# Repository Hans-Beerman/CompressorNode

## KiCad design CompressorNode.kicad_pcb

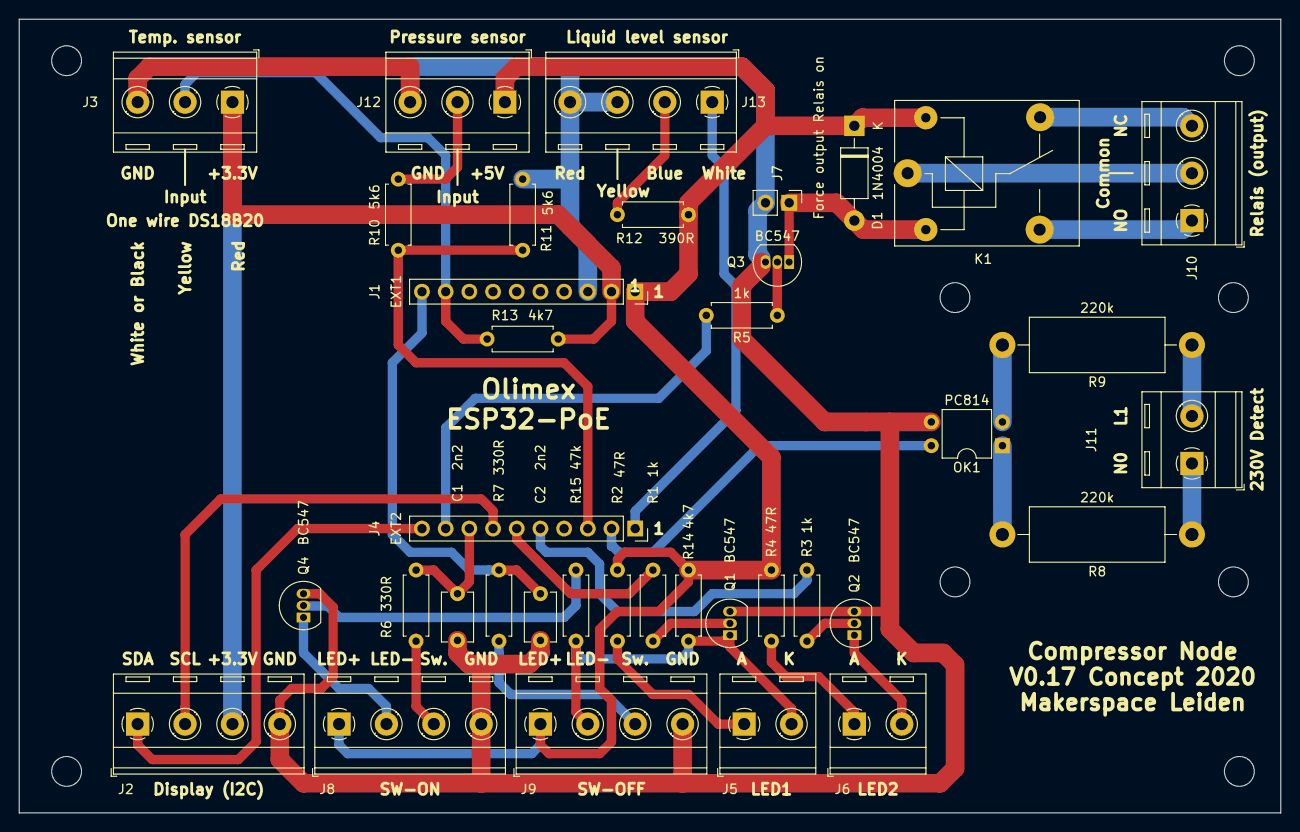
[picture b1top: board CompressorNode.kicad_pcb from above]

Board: 2 copper layers, 135.3 x 85.1 mm, 37 parts (0 on the bottom side), 35 nets.

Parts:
C1, C2: 2n2; C_Disc_D5.1mm_W3.2mm_P5.00mm
D1: 1N4004; D_DO-41_SOD81_P10.16mm_Horizontal
J1: EXT1; PinSocket_1x10_P2.54mm_Vertical
J2, J8, J9, J13: Screw_Terminal_01x04; TerminalBlock_RND_205-00289_1x04_P5.08mm_Horizontal
J3, J10, J12: Screw_Terminal_01x03; TerminalBlock_RND_205-00288_1x03_P5.08mm_Horizontal
J4: EXT2; PinSocket_1x10_P2.54mm_Vertical
J5, J6, J11: Screw_Terminal_01x02; TerminalBlock_RND_205-00287_1x02_P5.08mm_Horizontal
J7: Force output Relais on; PinHeader_1x02_P2.54mm_Vertical
K1: SANYOU_SRD_Form_C; Relay_SPDT_SANYOU_SRD_Series_Form_C
OK1: PC814; DIP-4_W7.62mm
Q1, Q2, Q3, Q4: BC547; TO-92_Inline
R1, R3, R5: 1k; R_Axial_DIN0207_L6.3mm_D2.5mm_P7.62mm_Horizontal
R2, R4: 47R; R_Axial_DIN0207_L6.3mm_D2.5mm_P7.62mm_Horizontal
R6, R7: 330R; R_Axial_DIN0207_L6.3mm_D2.5mm_P7.62mm_Horizontal
R8, R9: 220k; R_Axial_DIN0614_L14.3mm_D5.7mm_P20.32mm_Horizontal
R10, R11: 5k6; R_Axial_DIN0207_L6.3mm_D2.5mm_P7.62mm_Horizontal
R12: 390R; R_Axial_DIN0207_L6.3mm_D2.5mm_P7.62mm_Horizontal
R13, R14: 4k7; R_Axial_DIN0207_L6.3mm_D2.5mm_P7.62mm_Horizontal
R15: 47k; R_Axial_DIN0207_L6.3mm_D2.5mm_P7.62mm_Horizontal

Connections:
+3V3: J1.2, J2.3, J3.1, R13.2
+5V: D1.1, J1.1, J8.1, J9.1, J12.1, K1.5, R2.1, R4.1, R12.1, R14.1
GND: C1.2, C2.2, J1.3, J2.4, J3.3, J7.2, J8.4, J9.4, J12.3, J13.3, J13.4, OK1.3, Q1.3, Q2.3, Q3.3, Q4.3, R11.1
GPI35: J4.3, R10.1, R11.2
GPI36_U1RXD: J4.2, OK1.4
GPI39: J4.1, J13.1
GPIO4_U1TXD: J1.9, J3.2, R13.1
GPIO5_SPI_C5: C2.1, J1.10, R7.2
GPIO13_I2C-SDA: J2.1, J4.10
GPIO14_HS2_CLK: J4.9, R5.2
GPIO15_HS2_CMD: C1.1, J4.8, R6.2
GPIO16_I2C-SCL: J2.2, J4.7
GPIO32: J4.6, R1.2
GPIO33: J4.5, R3.2
unnamed: D1.2, J7.1, K1.2, Q3.1
unnamed: J5.1, R2.2
unnamed: J6.1, R4.2
unnamed: J6.2, Q2.1
unnamed: J8.2, Q4.1
unnamed: J8.3, R6.1
unnamed: J9.3, R7.1
unnamed: J10.1, K1.3
unnamed: J10.2, K1.1
unnamed: J10.3, K1.4
unnamed: J11.1, R8.1
unnamed: J11.2, R9.1
unnamed: J12.2, R10.2
unnamed: J13.2, R12.2
unnamed: OK1.1, R8.2
unnamed: OK1.2, R9.2
unnamed: Q1.2, R1.1
unnamed: Q2.2, R3.1
unnamed: Q3.2, R5.1
unnamed: Q4.2, R15.1
SWITCH-LED1-: J5.2, J9.2, Q1.1, R14.2, R15.2

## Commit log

2020-03-24 First release for GitHub
2020-03-24 LICENSE file added
2020-03-24 Adjusted R2 and R4 to 220R (instead of 1k)
2020-03-24 Added pdf of schematic drawing
2020-03-25 PCB designed
2020-03-27 corrected the groundplane and som PCB lines to create more distance to the 230V components
2020-03-29 corrected the distance between the two connectors for the ESP32-PoE
2020-03-30 LED Resistnow 47R to increase current for high power LEDs
2020-03-31 updated pdf
2020-04-01 Optocoupler was connected wrong
2020-04-01 R5 is now 150R because relais uses more current than expected
2020-04-02 resistor 4k7 added for DS18B20 temperature sensor
2020-04-02 moved a value in the schematic drawing for a better look and feel, same version
2020-04-02 Pressure sensor now connected to +5V instead of +3.3V
2020-04-02 Changed +3.3V text for pressure sensor to +5V on PCB, version not changed (v0.12)
2020-04-04 Labels on PCB corrected V0.13
2020-04-12 Moved some screw terminals to make room for USB cable. Also added screw terminal for power (out) V0.14 Concept
2020-04-19 Removed Power connector, added +5V output to the connectors for the switches V0.15 concept
2020-04-20 V0.16 concept: LED in switches are switched on or off to show which one can be pressed
2020-04-27 Changed some labels and R15 chanched to 47k V0.18
2020-04-27 V0.18: added a screw connector for safety, to switch of compressor in case a cable is disconnected
